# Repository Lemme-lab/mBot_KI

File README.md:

# mBot_KI

## Idee
Der mBot ist kein wirkliches selbstfahrendes Auto. Er kann Linien nur Folgen,
wenn sie durchgehend und direkt unter dem Fahrzeug sind.
Auch das er Hindernissen ausweichen kann ist eher trivial gelöst.
Er fährt erst gegen das Objekt und korrigiert dann erst. Die Idee der Erweiterung
ist das der mBot schon im Vorhinein Hindernisse erkennen kann
und diesen dann ausweicht. Auch die Linefollowing Funktion
soll Implemtiert werden. Der Input für beide Funktionen kommt von einer Kamera.

## Code
5.2.1 Erklärung Idee:
Das Ganze soll von einen Künstlichen Neuronalen Netzwerk gesteuert werden.
Genauer gesagt von einen CNN welches Trainingsdaten nimmt diese evaluiert Details findet,
die in jedem Bild vorhanden sind und diese in neuen Bildern findet. Das Ganze wird auf der Basis
von Keras Tensorflow gebaut.

## Input Algorithmus
Da die Bilder in Unterschiedlichen Größen kommen (Verschiedene Datasets),
müssen wir einen Algorithmus Implementieren der alle Bilder zu einer Größe
Hinunterschneidet. Wenn man den Input nicht auf eine Größe Hinunterschneidet,
kann das CNN diese nicht übernehmen (Interne Fehler in der Funktion). 

## Externes Training-Set:

## Input Algorithmus Teil.1
Die Bilder werden geladen und auf eine gewisse Größe (px) geschnitten.
Danach werden die Bilder mit den neuen zugeschnittenen Bildern überschrieben
und ein Blocked Array (X=Bilder, Y=Beschriftung) und ein Free Array mit der
Länge der beiden erstellt.

## Input Algorithmus Teil.2
Die zugeschnittenen Bilder werden eingelesen und in Farbwerte umgewandelt.
Danach werden sie in den zuvor erstellten Arrays gespeichert.
Hinter den ‚#‘ findet man Test Funktionen die das Array oder die Bilder
mit ihrer Überschrift ausgeben.
Zuletzt wird noch die Anzahl an Blocked und Free Images angezeigt.

## Training-Code
Der Haupt-Code, hier werden alle Bilder verarbeitet.
Im model.fit Teil wird das Neural Network mit 32 Bilder pro Input
auf 200 Epochen trainiert. Der erste große Teil sind Layers.
Diese helfen die accuracy zu steigern. Am Ende wird das ganze nochmal
Compiled und zusammengefasst.

## Evaluation, Testen, Speichern
Zuletzt wird das Model nochmal Compiled und Evaluiert. Dann kann man dem
Neural Network ein Bild geben welches es dann Predicted (Free/Blocked).
Am Ende speichert man das System als HDF5 gespeichert. 

# Hardware
##CPU
Durch die geringe „CPU-Leistung“ des Arduinos müsste man auf einen
Raspberry PI 4 umsteigen. Die Implementierung der Live Kamera wäre
dadurch auch viel einfacher.

## Kamera
Die PI-Cam wurde ausgesucht für das Live Video.
Sie kann jedoch auch durch die Wireless Funktion sehr gut
zum Trainingsdaten sammeln eingesetzt werden.
Cam und Controll Code:

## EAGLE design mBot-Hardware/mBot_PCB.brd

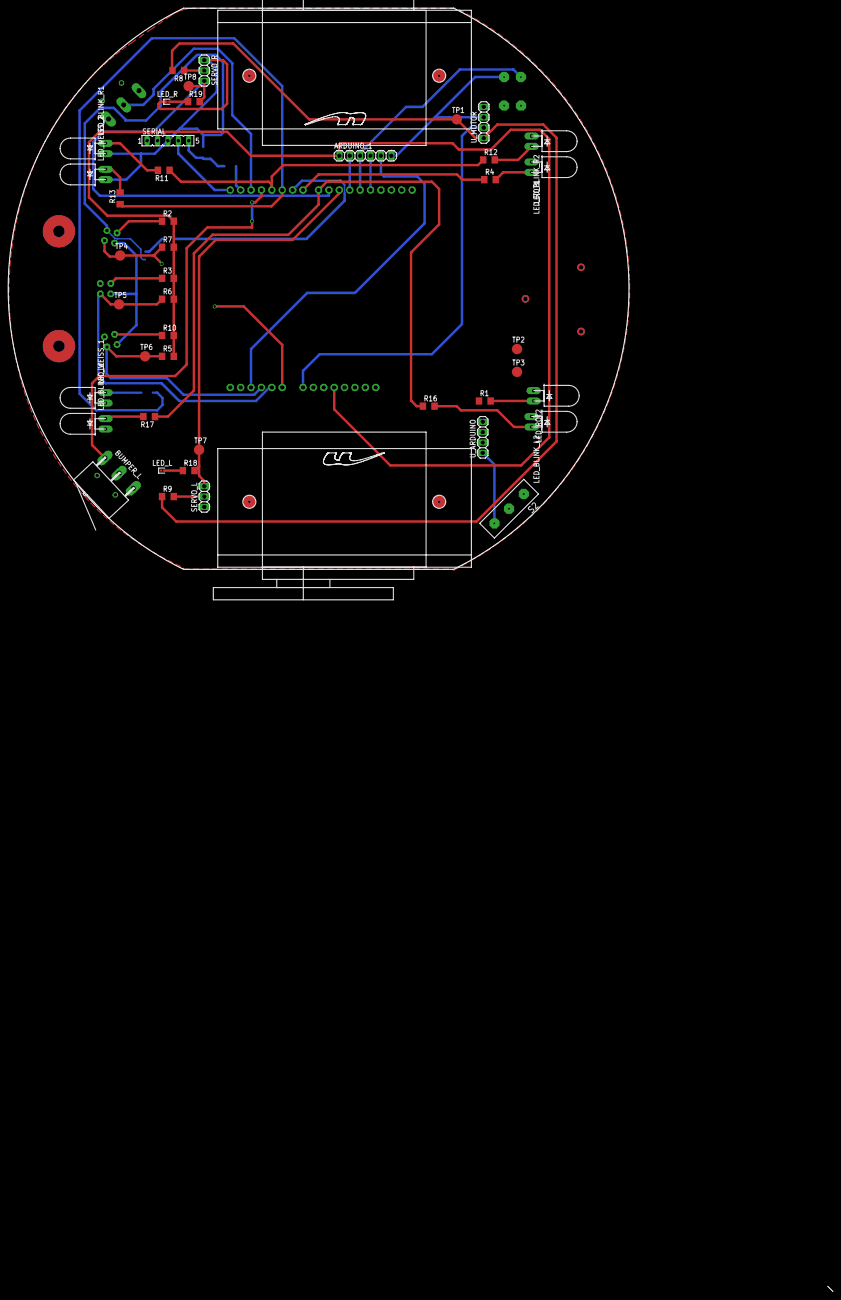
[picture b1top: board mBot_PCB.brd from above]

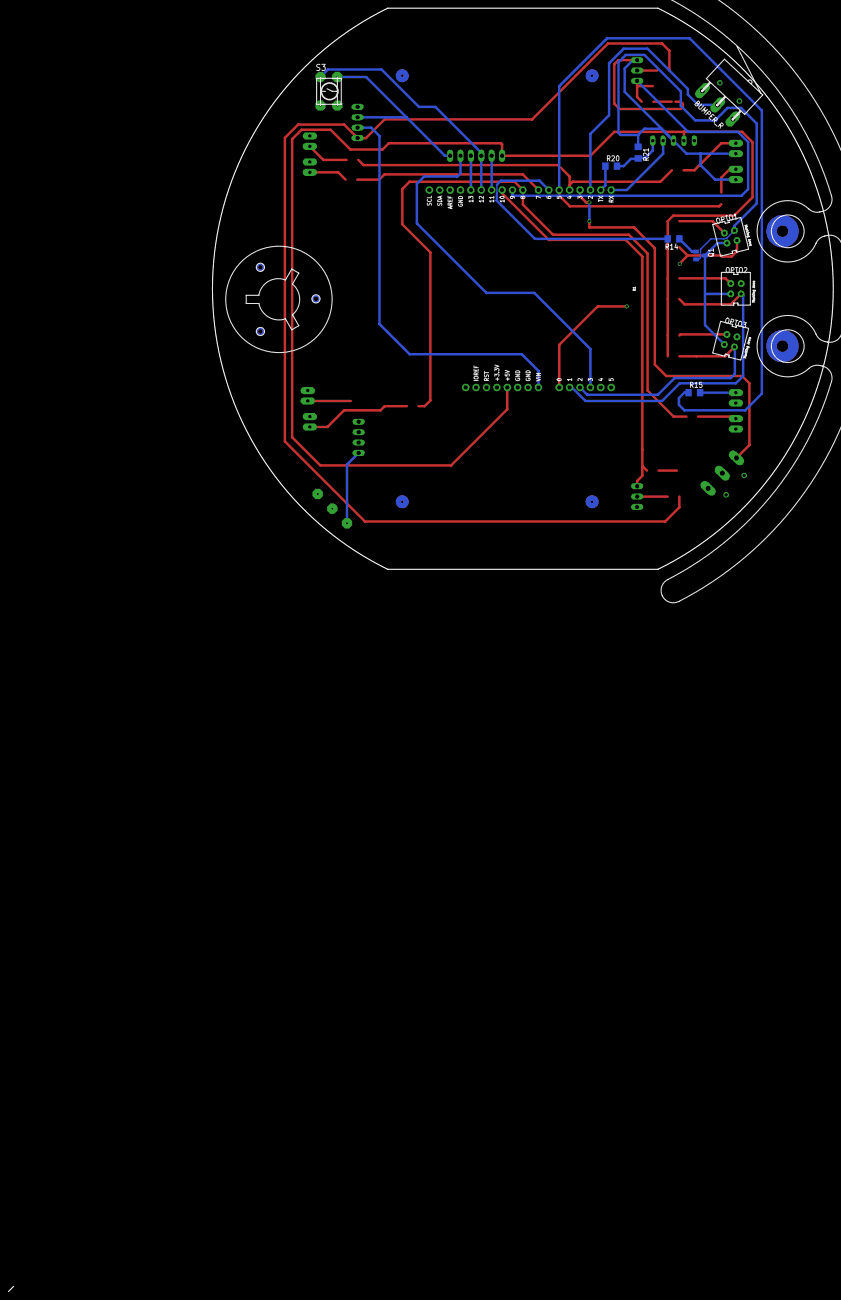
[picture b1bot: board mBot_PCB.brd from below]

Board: 2 copper layers, 151.7 x 137.2 mm, 58 parts (12 on the bottom side), 42 nets.

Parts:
ARDUINO_1: 1X06
B1: ARDUINO_UNO_R3_SHIELDBASIC; UNO_R3_SHIELD
BUMPER_L: MIKROSCHALTER_H_L
BUMPER_R: MIKROSCHALTER_H_L
E$1: STANDARDSERVO01
E$2: STANDARDSERVO_LINKS-01
E$3: BALLCASTER26MM
E$4: BUMPER_R80
LED_BLINK_L1, LED_BLINK_L2: gelb; LED5MM-LGD
LED_BLINK_R1, LED_BLINK_R2: gelb; LED5MM-LGD
LED_L: CHIP-FLAT-B_0402; LEDC1005X25N_FLAT-B
LED_R: CHIP-FLAT-B_0402; LEDC1005X25N_FLAT-B
LED_ROT1, LED_ROT2: rot; LED5MM-LGD
LED_WEISS_1, LED_WEISS_2: weiss; LED5MM-LGD
OPTO1, OPTO2, OPTO3: CNY70; 4
Q1: BC818-40SMD; SOT23-BEC
R1, R4, R11, R12, R16, R17, R18, R19: 220R; R1206
R2, R3, R10, R13, R15: 150R; R1206
R5, R6, R7, R21: 10k; R1206
R8, R9: 1R8; R1206
R14: 3k3; R1206
R20: 4k7; R1206
S2: 1XUM
S3: MINITAST2
SERIAL: FE05-1
SERVO_L: 1X03
SERVO_R: 1X03
TP1, TP2, TP3, TP4, TP5, TP6, TP7, TP8: TPB2,54; B2,54
U_ARDUINO: 1X04
U_MOTOR: 1X04

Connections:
+5V: ARDUINO_1.1, B1.5V, R2.2, R3.2, R5.2, R6.2, R7.2, R10.2, SERIAL.2
+UB: R8.2, R9.1, TP1.TP, U_MOTOR.1
GND: ARDUINO_1.6, B1.GND@0, B1.GND@1, BUMPER_L.NO, LED_BLINK_L1.K, LED_BLINK_L2.K, LED_BLINK_R2.K, LED_L.C, LED_ROT1.K, LED_ROT2.K, LED_WEISS_1.K, OPTO3.E, S3.2, SERVO_L.1, TP2.TP, TP3.TP, U_ARDUINO.3, U_MOTOR.3
unnamed: B1.RX, SERIAL.4
unnamed: B1.TX, R20.1
unnamed: B1.A0, OPTO1.C, R7.1, TP4.TP
unnamed: OPTO1.A, R2.1
unnamed: B1.A1, OPTO2.C, R6.1, TP5.TP
unnamed: B1.A2, OPTO3.C, R5.1, TP6.TP
unnamed: OPTO2.A, R3.1
unnamed: OPTO3.A, R10.1
unnamed: OPTO1.K, OPTO2.K, OPTO3.K, Q1.C
unnamed: Q1.B, R14.1
unnamed: B1.D6, R14.2
unnamed: R20.2, R21.2, SERIAL.5
unnamed: ARDUINO_1.2, B1.D11
unnamed: ARDUINO_1.3, B1.D12, S3.1
unnamed: ARDUINO_1.4, B1.D13
unnamed: ARDUINO_1.5, B1.A3
unnamed: B1.D10, R18.2, SERVO_L.3, TP7.TP
unnamed: LED_L.A, R18.1
unnamed: LED_R.A, R19.1
unnamed: R9.2, SERVO_L.2
unnamed: B1.D9, R19.2, SERVO_R.3, TP8.TP
unnamed: B1.D2, BUMPER_R.NO
unnamed: B1.D3, BUMPER_L.COM
unnamed: R8.1, SERVO_R.2
unnamed: B1.D4, R11.1, R12.1
unnamed: LED_WEISS_1.A, R15.2
unnamed: B1.D7, R1.1, R4.1
unnamed: B1.D8, R16.1, R17.1
unnamed: LED_ROT1.A, R4.2
unnamed: LED_ROT2.A, R1.2
unnamed: LED_BLINK_L1.A, R17.2
unnamed: LED_BLINK_L2.A, R16.2
unnamed: LED_WEISS_2.A, R13.2
unnamed: B1.D5, R13.1, R15.1
unnamed: LED_BLINK_R2.A, R12.2
unnamed: LED_BLINK_R1.A, R11.2
unnamed: S2.2, U_ARDUINO.1
S$1: LED_BLINK_R1.K, LED_R.C, LED_WEISS_2.K, OPTO1.E, Q1.E, R21.1, SERIAL.3, SERVO_R.1
V+: B1.VIN, S2.W, U_MOTOR.2

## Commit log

2021-09-23 init
2021-09-23 test
2021-09-23 changed to main
2021-09-23 added model
2021-11-14 Added 3D-Models/Hardware

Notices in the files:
parts and their libraries:
SparkFun-Boards: Licensing: Creative Commons ShareAlike 4.0 International - https://creativecommons.org/licenses/by-sa/4.0
